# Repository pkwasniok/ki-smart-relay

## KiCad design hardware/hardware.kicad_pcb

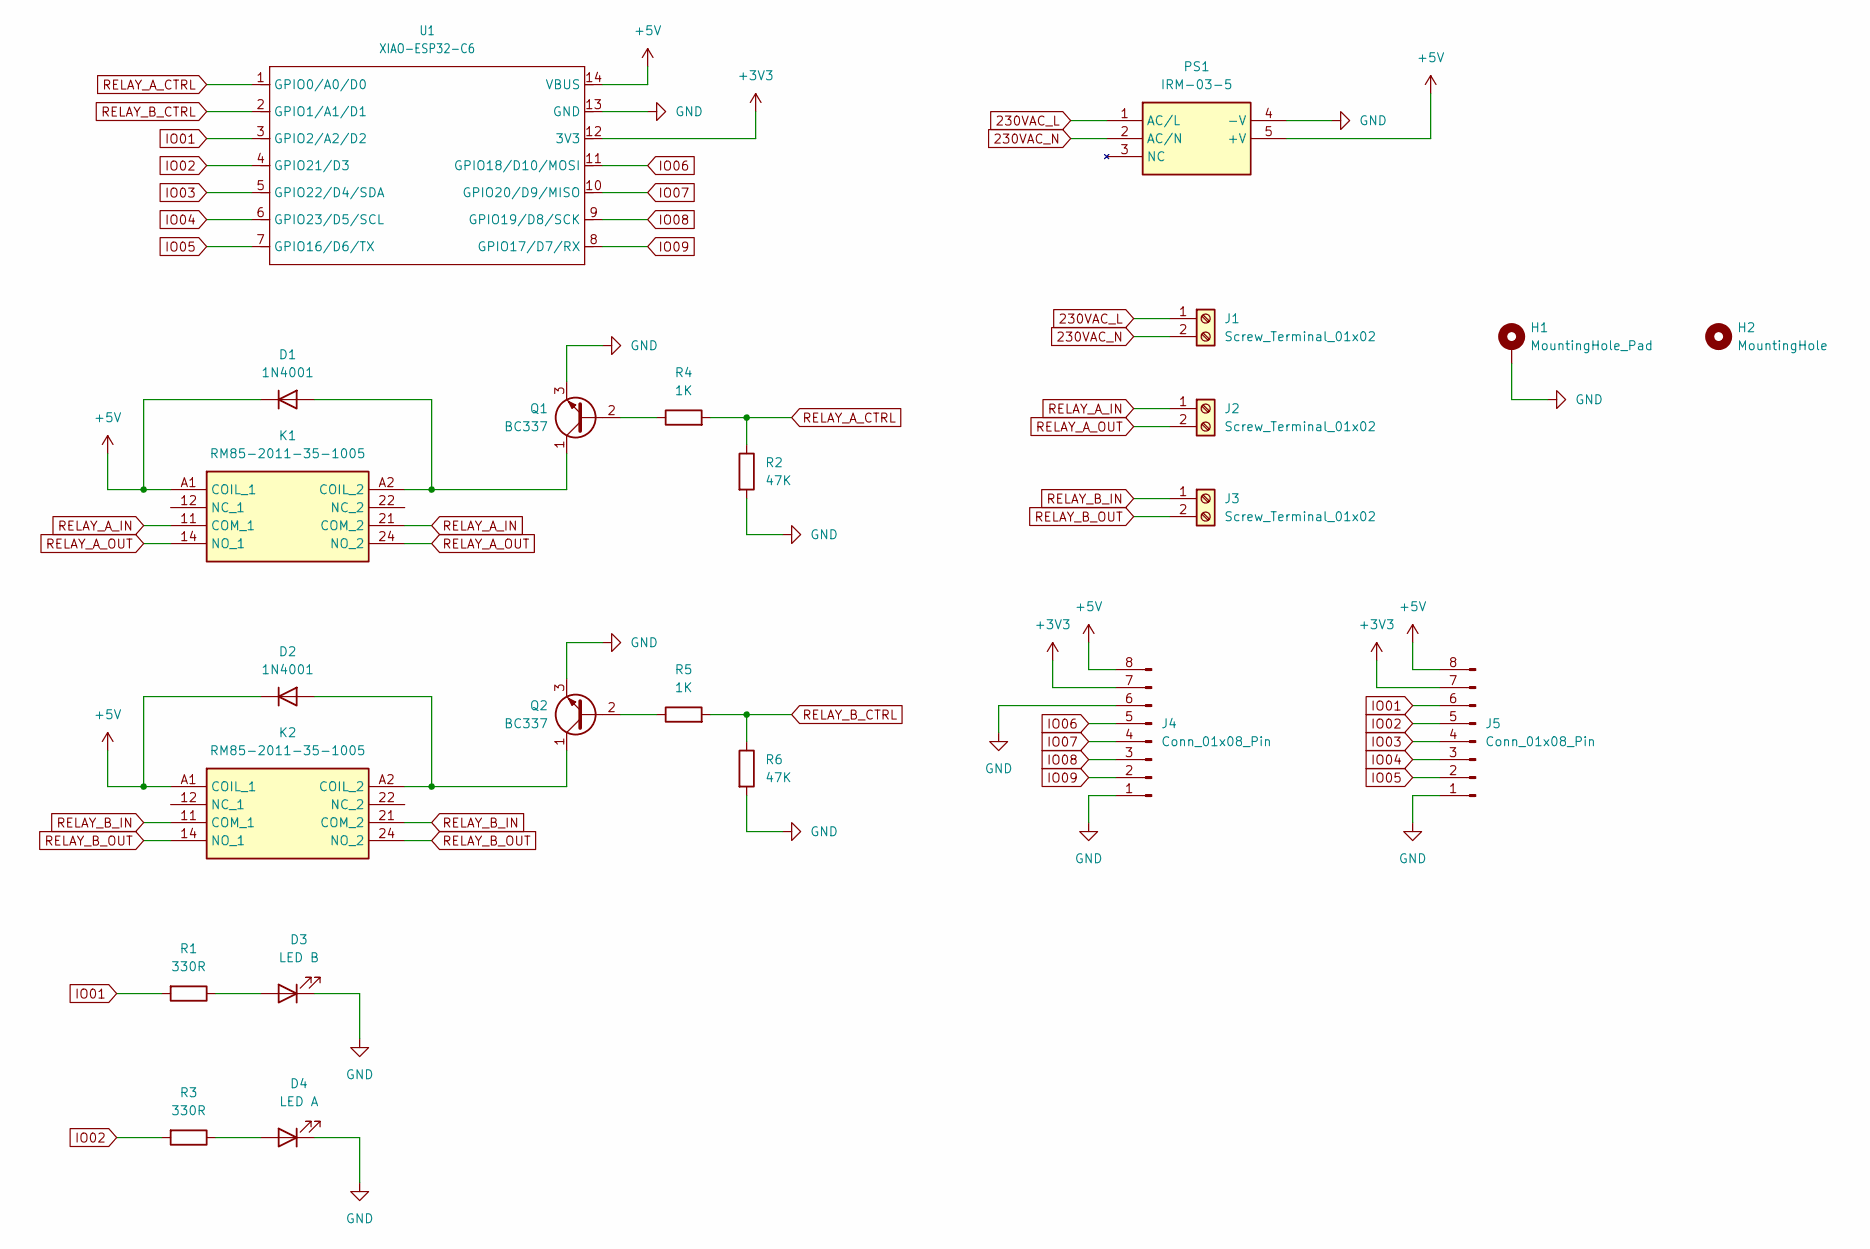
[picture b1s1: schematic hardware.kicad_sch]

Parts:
D1, D2: 1N4001; D_A-405_P7.62mm_Horizontal
D3: LED B; LED_D3.0mm
D4: LED A; LED_D3.0mm
H1: MountingHole_Pad; MountingHole_2.2mm_M2_Pad
H2: MountingHole; MountingHole_2.2mm_M2
J1, J2, J3: Screw_Terminal_01x02; SHDR2W100P0X500_1X2_1000X780X1020P
J4, J5: Conn_01x08_Pin; PinHeader_1x08_P2.54mm_Vertical
K1, K2: RM85-2011-35-1005; relpol_rm85_2011_35_1005; Manufacturer_Part_Number RM85-2011-35-1005
PS1: IRM-03-5; IRM0312; Manufacturer_Part_Number IRM-03-5
Q1, Q2: BC337; TO-92_Inline
R1, R3: 330R; R_Axial_DIN0204_L3.6mm_D1.6mm_P7.62mm_Horizontal
R2, R6: 47K; R_Axial_DIN0204_L3.6mm_D1.6mm_P7.62mm_Horizontal
R4, R5: 1K; R_Axial_DIN0204_L3.6mm_D1.6mm_P7.62mm_Horizontal
U1: XIAO-ESP32-C6; seeed_studio_xiao_esp32c6_dip

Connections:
230VAC_L: J1.1, PS1.1 (AC/L)
230VAC_N: J1.2, PS1.2 (AC/N)
+3V3: J4.7, J5.7, U1.12 (3V3)
+5V: D1.1 (K), D2.1 (K), J4.8, J5.8, K1.A1 (COIL_1), K2.A1 (COIL_1), PS1.5 (+V), U1.14 (VBUS)
GND: D3.1 (K), D4.1 (K), H1.1, J4.1, J4.6, J5.1, PS1.4 (-V), Q1.3 (E), Q2.3 (E), R2.2, R6.2, U1.13 (GND)
IO01: J5.6, R1.2, U1.3 (GPIO2/A2/D2)
IO02: J5.5, R3.2, U1.4 (GPIO21/D3)
IO03: J5.4, U1.5 (GPIO22/D4/SDA)
IO04: J5.3, U1.6 (GPIO23/D5/SCL)
IO05: J5.2, U1.7 (GPIO16/D6/TX)
IO06: J4.5, U1.11 (GPIO18/D10/MOSI)
IO07: J4.4, U1.10 (GPIO20/D9/MISO)
IO08: J4.3, U1.9 (GPIO19/D8/SCK)
IO09: J4.2, U1.8 (GPIO17/D7/RX)
unnamed: D1.2 (A), K1.A2 (COIL_2), Q1.1 (C)
unnamed: D2.2 (A), K2.A2 (COIL_2), Q2.1 (C)
unnamed: D3.2 (A), R1.1
unnamed: D4.2 (A), R3.1
unnamed: Q1.2 (B), R4.1
unnamed: Q2.2 (B), R5.1
RELAY_A_CTRL: R2.1, R4.2, U1.1 (GPIO0/A0/D0)
RELAY_A_IN: J2.1, K1.11 (COM_1), K1.21 (COM_2)
RELAY_A_OUT: J2.2, K1.14 (NO_1), K1.24 (NO_2)
RELAY_B_CTRL: R5.2, R6.1, U1.2 (GPIO1/A1/D1)
RELAY_B_IN: J3.1, K2.11 (COM_1), K2.21 (COM_2)
RELAY_B_OUT: J3.2, K2.14 (NO_1), K2.24 (NO_2)

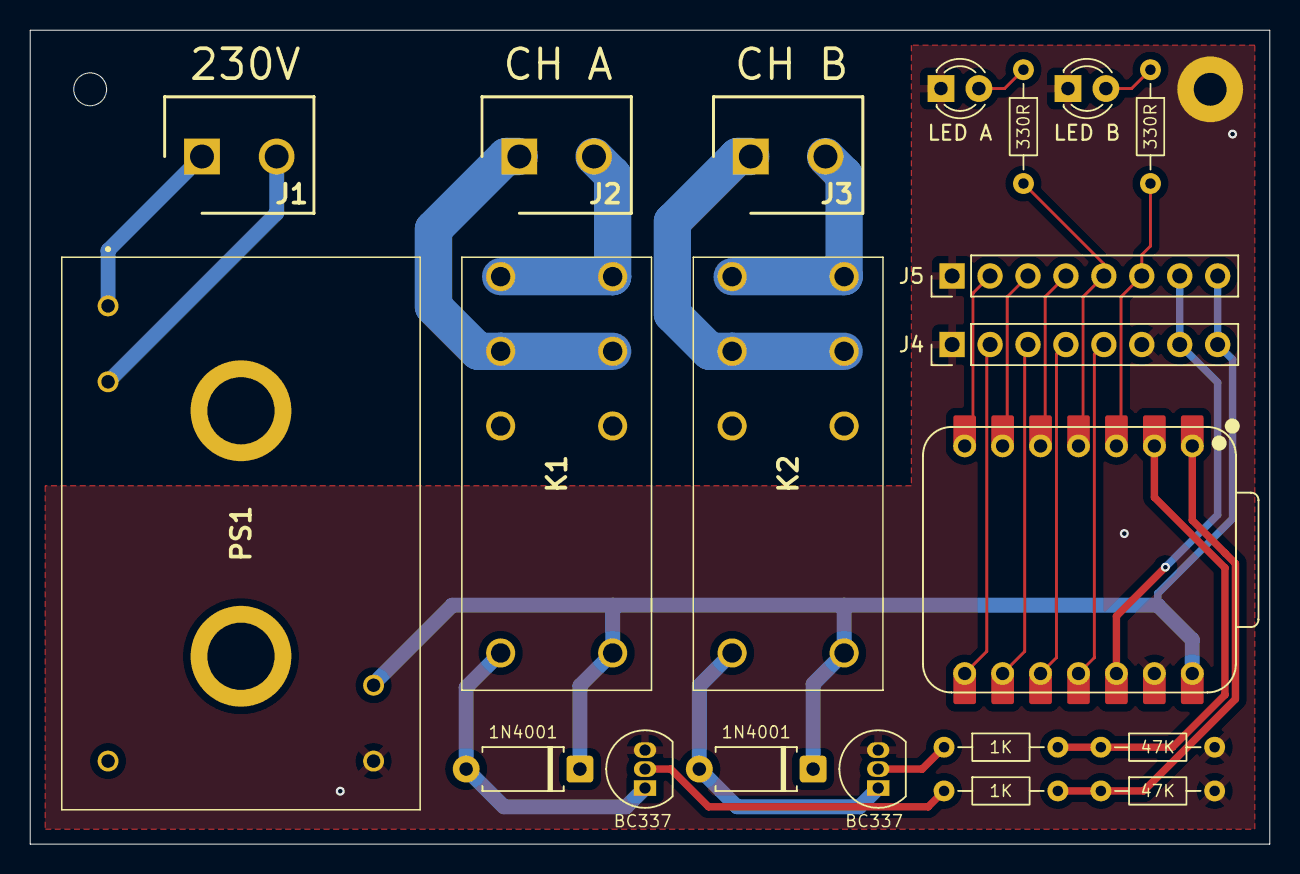
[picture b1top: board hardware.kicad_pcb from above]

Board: 2 copper layers, 83.0 x 54.5 mm, 23 parts (0 on the bottom side), 26 nets.

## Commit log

2025-05-11 ESP-IDF configuration for ESP32-C6
2025-05-11 Added KiCad libraries
2025-05-11 Started working on relay driving circuit
2025-05-12 Changed transitior orientation
2025-05-12 Added relay flyback diode
2025-05-12 Added pull-down resistor to relay control signal
2025-05-12 Added power supply
2025-05-12 Added second relay
2025-05-12 Added temperature sensor
2025-05-12 Added leds and connectors
2025-05-12 Started working on PCB
2025-05-12 Improved PCB layout
2025-05-16 Started working on new PCB layout
2025-05-17 New layout with new screw terminals
2025-05-17 Removed DS18B20 temp sensor
2025-05-17 Started working on PCB traces
2025-05-23 Removed unnecessary resistors
    Removec resistors limiting current flowing through relay coils
2025-05-23 Updated PCB footprint layout
    Updatec PCB layout after removing resistors
2025-05-27 Added PCB traces
2025-05-27 Added GND fill zone
2025-05-27 Added mounting holes
2025-05-27 Updated screw terminals
2025-05-27 Finished PCB layout and traces
2025-05-27 Finished PCB silkscreen
2025-05-27 Added headers for extra gpios
2025-05-27 Added status LEDs
2025-05-27 Removed solder mask from 230V HP traces
2025-06-11 Device identifier generator
2025-06-11 Merged with old relay project
2025-06-11 Identifier generation during setup
2025-06-12 First software version
2025-06-14 Wifi APs scanner with RSSI and channels
2025-06-14 Enable ceramic antenna during setup
2025-06-14 Relay testing procedure
2025-06-14 Custom utils/delay library
2025-06-14 Removed dead code
2025-06-14 Changed from ceramic antenna to ufl antenna
2025-06-14 Wifi antenna switch driver
2025-06-14 Project structure
2025-08-03 improved functionality
2025-08-04 split functionality into different tasks
2025-08-05 finished refactoring
2025-08-05 publish relay status to mqtt topic
2025-08-05 add more config options
2025-08-05 removed unused code
